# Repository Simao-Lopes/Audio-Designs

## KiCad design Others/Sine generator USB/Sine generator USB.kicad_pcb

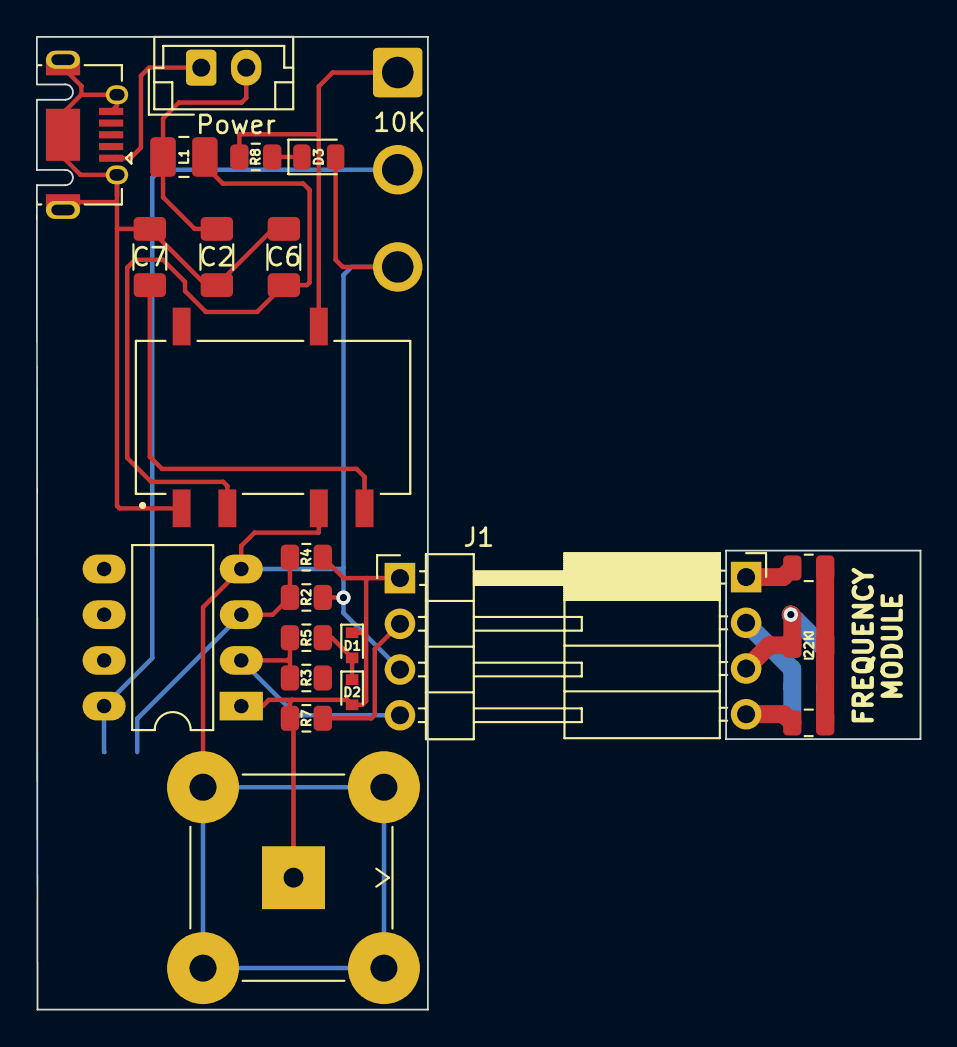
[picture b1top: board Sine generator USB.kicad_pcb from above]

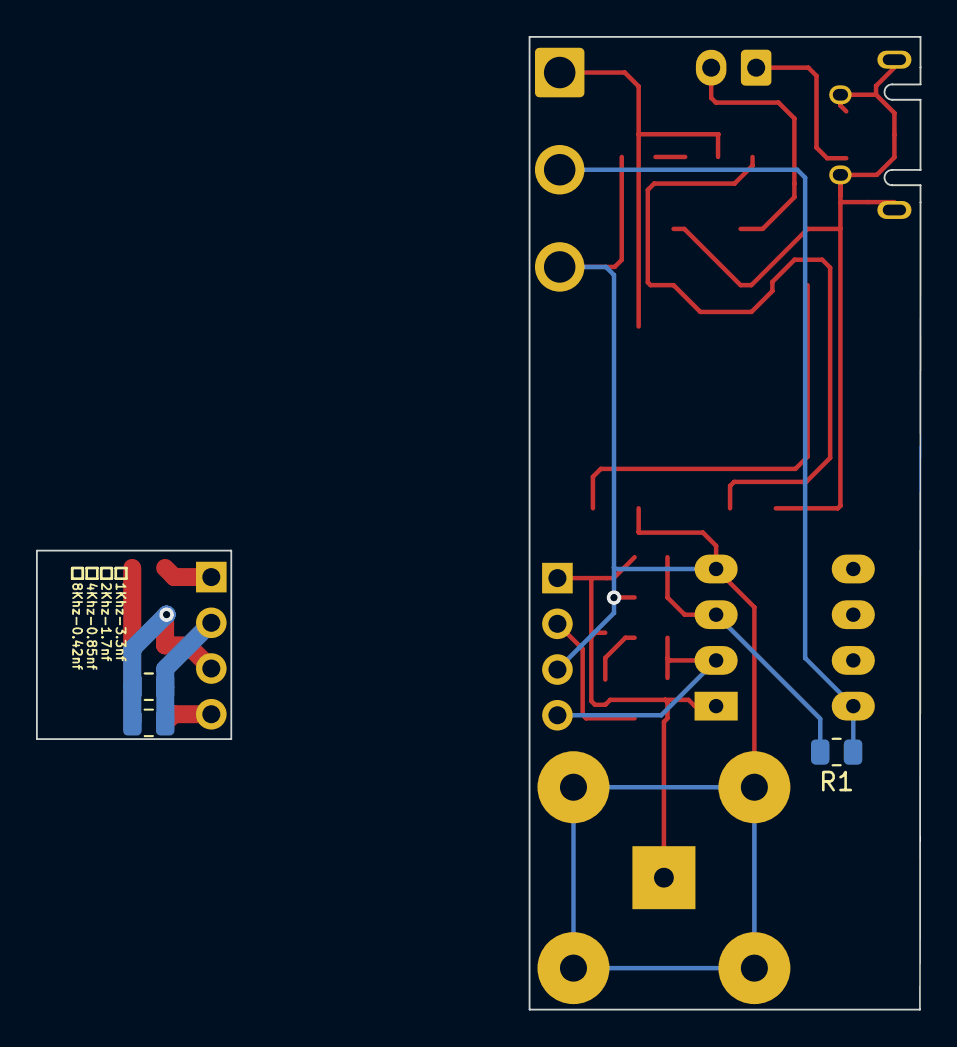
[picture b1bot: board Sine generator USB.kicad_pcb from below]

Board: 2 copper layers, 49.1 x 54.0 mm, 27 parts (3 on the bottom side), 19 nets.

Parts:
10K: 10K; SolderWire-1sqmm_1x03_P5.4mm_D1.4mm_OD2.7mm
22K: 22k; R_0805_2012Metric
C1, C3, C4, C5: 0.01uf; R_0805_2012Metric
C2, C6: 4u7; C_1206_3216Metric_Pad1.33x1.80mm_HandSolder
C7: 1nf/4kv; C_1206_3216Metric_Pad1.33x1.80mm_HandSolder
D1, D2: 1N4148; D_SOD-523
D3: LED; LED_0805_2012Metric
J1: Board In; PinHeader_1x04_P2.54mm_Horizontal
J2: Freq_board; PinSocket_1x04_P2.54mm_Horizontal
J3: Conn_Coaxial; BNC_TEConnectivity_1478035_Horizontal
J4: USB_B_Mini; USB_Micro-AB_Molex_47590-0001
L1: 6.8uh; L_1008_2520Metric_Pad1.43x2.20mm_HandSolder
Power: SW_DIP_x01; JST_EH_B2B-EH-A_1x02_P2.50mm_Vertical
R1, R2, R8: 10K; R_0805_2012Metric
R3: 47K; R_0805_2012Metric
R4: 300K; R_0805_2012Metric
R5: 470K; R_0805_2012Metric
R7: 47k; R_0805_2012Metric
U1: LM358; DIP-8_W7.62mm_LongPads
U2: PESE1-S5-D12-M; CONV_PESE1-S5-D12-M

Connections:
/Gnd_board: 22K.2, C1.1, C4.1, J2.3
GND: 10K.3, D3.2 (A), J1.3, J3.2 (Ext), R2.2, U1.4 (V-), U2.4 (0V)
unnamed: C1.2, C4.2, J2.2
unnamed: C2.2, C6.1, C7.1, J4.5 (GND), J4.6 (Shield), U2.1 (VIN-)
unnamed: C3.1, J2.4
unnamed: 22K.1, C3.2, C5.1
unnamed: C5.2, J2.1
unnamed: C6.2, L1.2, U2.2 (VIN+)
unnamed: C7.2, U2.5 (VOUT-)
unnamed: D1.1 (K), D2.2 (A), J1.1, J3.1 (In), R4.2, R7.2, U1.1
unnamed: D1.2 (A), D2.1 (K), R5.2
unnamed: D3.1 (K), R8.1
unnamed: J1.2, R3.2, R7.1
unnamed: J1.4, R3.1, R5.1, U1.2 (-)
unnamed: 10K.2, R1.1, U1.8 (V+)
unnamed: R1.2, R2.1, R4.1, U1.3 (+)
unnamed: 10K.1, R8.2, U2.7 (VOUT+)
unnamed: J4.1 (VBUS), Power.1
unnamed: C2.1, L1.1, Power.2

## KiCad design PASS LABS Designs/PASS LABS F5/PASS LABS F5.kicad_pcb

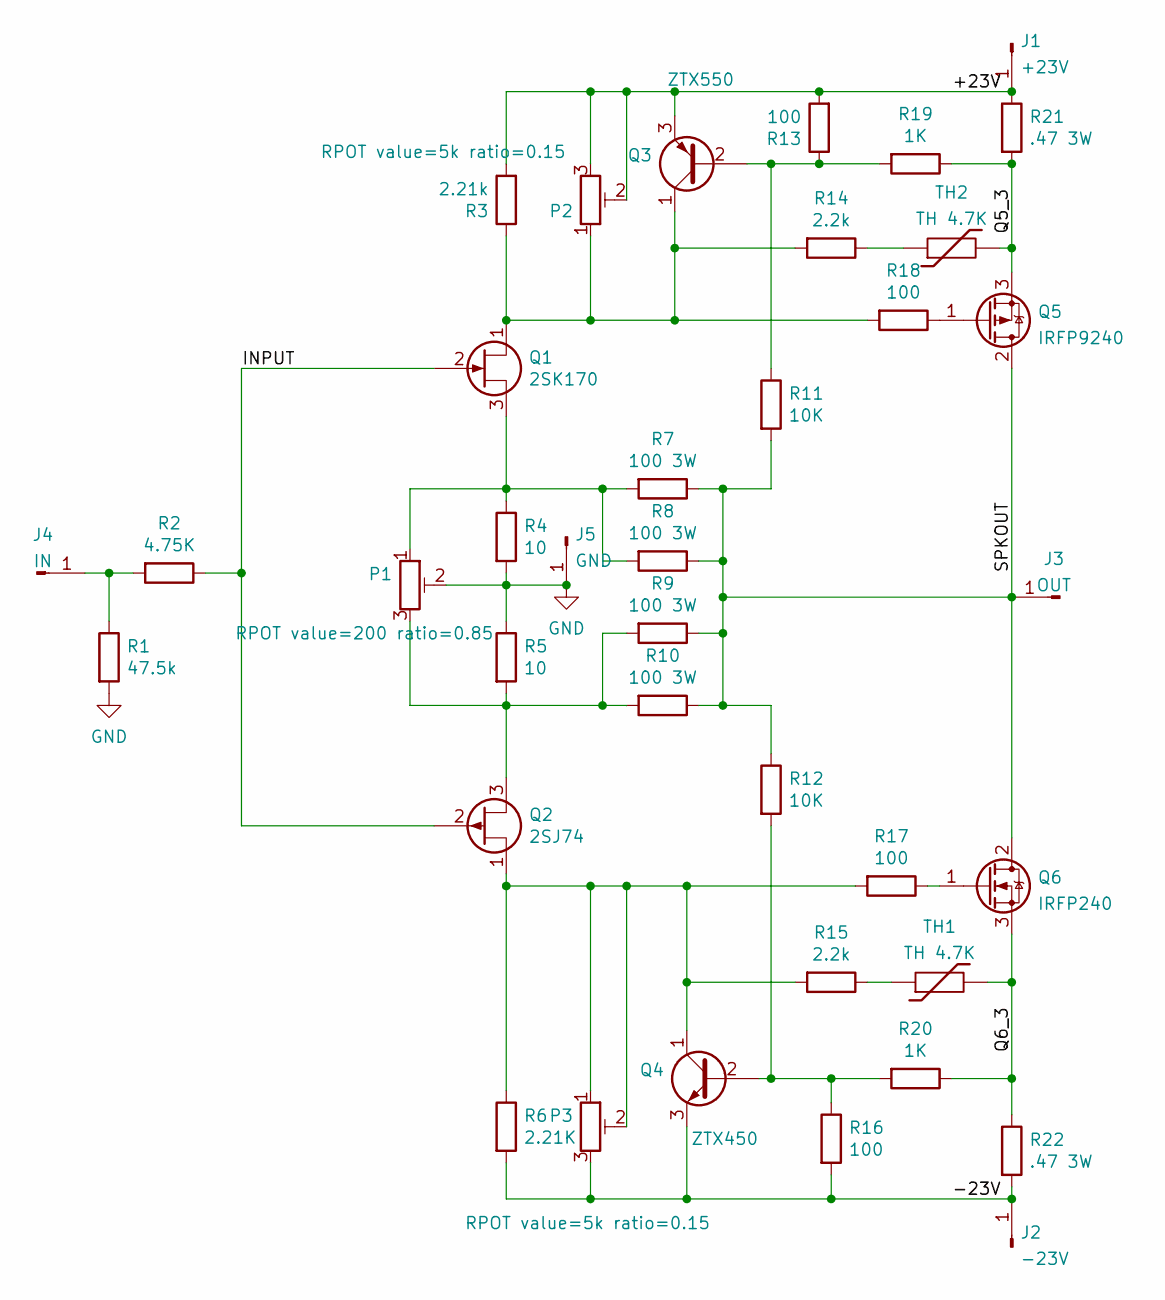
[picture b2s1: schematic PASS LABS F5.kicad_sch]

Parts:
J1: +23V; M4_Screw_Terminal
J2: -23V; M4_Screw_Terminal
J3: OUT; M4_Screw_Terminal
J4: IN; M4_Screw_Terminal
J5: GND; M4_Screw_Terminal
P1: 200; TRIM_3362P-1-103
P2: 5K; TRIM_3362P-1-103
P3: 5k; TRIM_3362P-1-103
Q1: 2SK170; TO-92L_Wide
Q2: 2SJ74; TO-92L_Wide
Q3: ZTX550; TO-92L_Wide
Q4: ZTX450; TO-92L_Wide
Q5: IRFP9240; TO-247-3_Vertical
Q6: IRFP240; TO-247-3_Vertical
R1: 47.5k; R_Axial_DIN0207_L6.3mm_D2.5mm_P10.16mm_Horizontal
R2: 4.75K; R_Axial_DIN0207_L6.3mm_D2.5mm_P10.16mm_Horizontal
R3: 2.21k; R_Axial_DIN0207_L6.3mm_D2.5mm_P10.16mm_Horizontal
R4, R5: 10; R_Axial_DIN0207_L6.3mm_D2.5mm_P10.16mm_Horizontal
R6: 2.21K; R_Axial_DIN0207_L6.3mm_D2.5mm_P10.16mm_Horizontal
R7, R8, R9, R10: 100 3W; R_Axial_DIN0411_L9.9mm_D3.6mm_P15.24mm_Horizontal
R11, R12: 10K; R_Axial_DIN0207_L6.3mm_D2.5mm_P10.16mm_Horizontal
R13, R16, R17, R18: 100; R_Axial_DIN0207_L6.3mm_D2.5mm_P10.16mm_Horizontal
R14, R15: 2.2k; R_Axial_DIN0207_L6.3mm_D2.5mm_P10.16mm_Horizontal
R19, R20: 1K; R_Axial_DIN0207_L6.3mm_D2.5mm_P10.16mm_Horizontal
R21, R22: .47 3W; R_Axial_DIN0411_L9.9mm_D3.6mm_P15.24mm_Horizontal
TH1, TH2: TH 4.7K; C_Disc_D3.0mm_W2.0mm_P2.50mm

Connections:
/+23V: J1.1, P2.2, P2.3, Q3.3 (E), R3.2, R13.2, R21.1
/-23V: J2.1, P3.3, Q4.3 (E), R6.2, R16.2, R22.2
/INPUT: Q1.2 (G), Q2.2 (G), R2.1
/Q5_3: Q5.3 (S), R19.1, R21.2, TH2.2
/Q6_3: Q6.3 (S), R20.1, R22.1, TH1.2
/SPKOUT: J3.1, Q5.2 (D), Q6.2 (D), R7.1, R8.1, R9.1, R10.1, R11.2, R12.1
GND: J5.1, P1.2, R1.2, R4.2, R5.1; also elsewhere on the board
unnamed 7: J4.1, R1.1, R2.2; also elsewhere on the board
unnamed: P1.1, Q1.3 (S), R4.1, R7.2, R8.2
unnamed: P1.3, Q2.3 (D), R5.2, R9.2, R10.2
unnamed: P2.1, Q1.1 (D), Q3.1 (C), R3.1, R14.2, R18.2
unnamed: P3.1, P3.2, Q2.1 (S), Q4.1 (C), R6.1, R15.2, R17.2
unnamed: Q3.2 (B), R11.1, R13.1, R19.2
unnamed: Q4.2 (B), R12.2, R16.1, R20.2
unnamed: Q5.1 (G), R18.1
unnamed: Q6.1 (G), R17.1
unnamed: R14.1, TH2.1
unnamed: R15.1, TH1.1

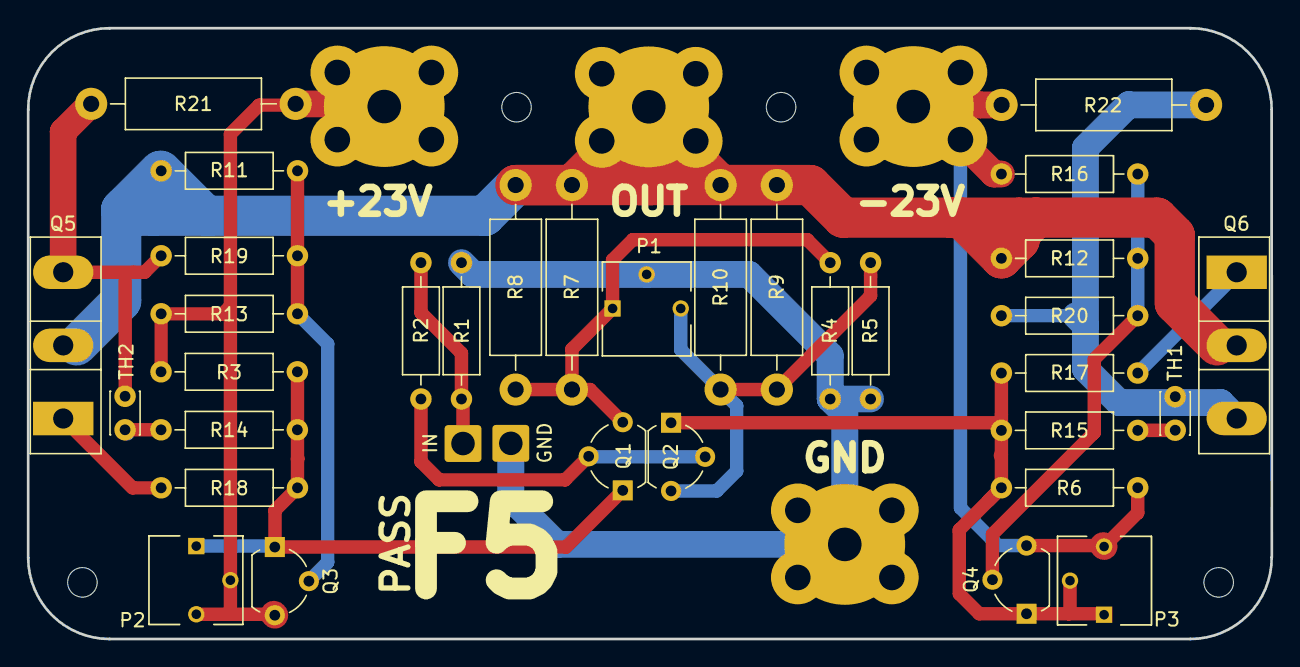
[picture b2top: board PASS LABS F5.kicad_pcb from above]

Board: 2 copper layers, 92.7 x 45.5 mm, 39 parts (0 on the bottom side), 18 nets.

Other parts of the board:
GND: IN; SolderWire-1sqmm_1x01_D1.4mm_OD2.7mm
IN: IN; SolderWire-1sqmm_1x01_D1.4mm_OD2.7mm

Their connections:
GND: GND.1; also elsewhere on the board
unnamed 7: IN.1; also elsewhere on the board

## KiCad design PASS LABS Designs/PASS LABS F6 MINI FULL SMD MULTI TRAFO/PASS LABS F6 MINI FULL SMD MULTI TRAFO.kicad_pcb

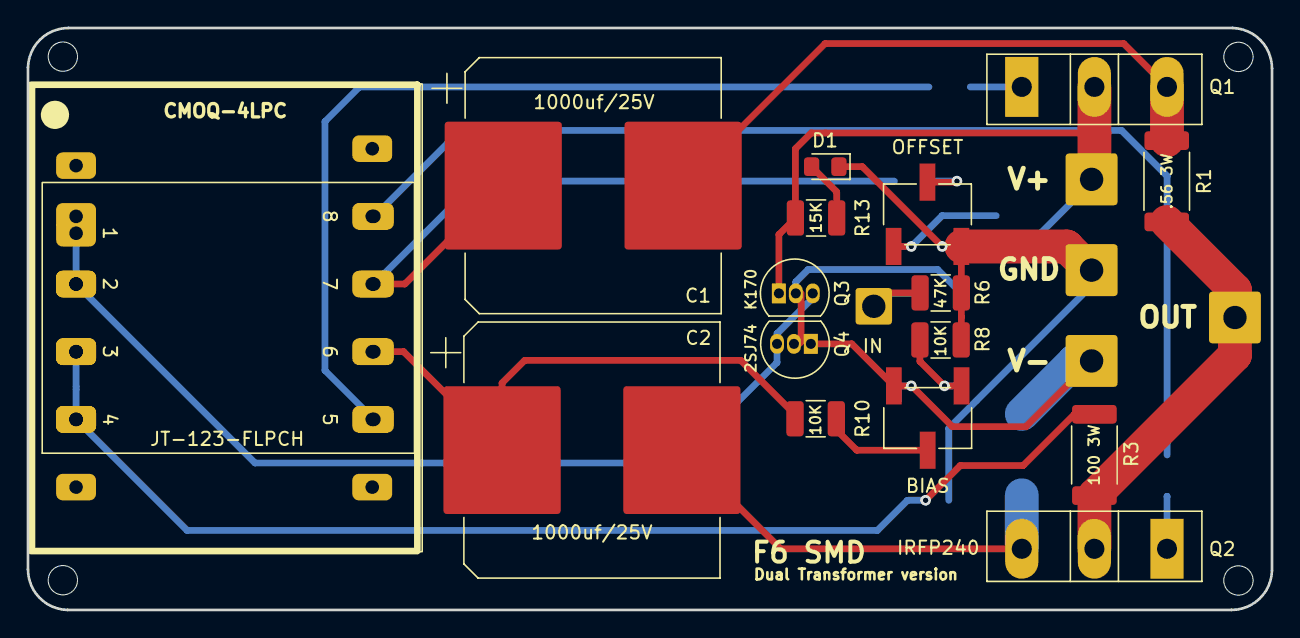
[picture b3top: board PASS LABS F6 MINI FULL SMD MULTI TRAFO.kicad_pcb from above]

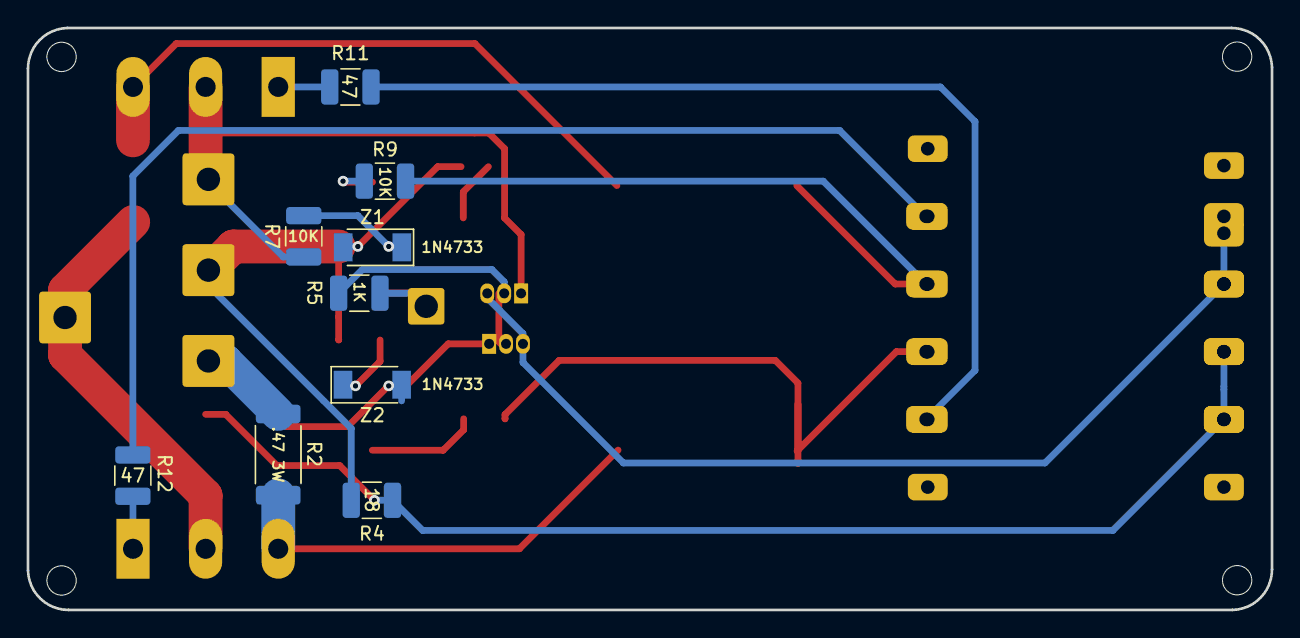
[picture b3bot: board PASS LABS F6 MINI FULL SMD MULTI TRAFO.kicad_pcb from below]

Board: 2 copper layers, 93.4 x 43.7 mm, 30 parts (9 on the bottom side), 21 nets.

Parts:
BIAS: R_Potentiometer_US; Potentiometer_Bourns_3269W_Vertical
C1, C2: 1000uf/25V; CP_Elec_18x17.5
D1: LED; LED_0805_2012Metric_Pad1.15x1.40mm_HandSolder
GND: GND; SolderWire-1sqmm_1x01_D1.4mm_OD3.9mm
IN: SG IN; SolderWire-1sqmm_1x01_D1.4mm_OD2.7mm
OFFSET: R_Potentiometer_US; Potentiometer_Bourns_3269W_Vertical
OUT: OUT; SolderWire-1sqmm_1x01_D1.4mm_OD3.9mm
Q1, Q2: IRFP240; TO-247-3_Vertical
Q3: K170; TO-92L_Inline
Q4: 2SJ74; TO-92L_Inline
R1: .56 3W; R_2512_6332Metric_Pad1.40x3.35mm_HandSolder
R2: .47 3W; R_2512_6332Metric_Pad1.40x3.35mm_HandSolder
R3: 100 3W; R_2512_6332Metric_Pad1.40x3.35mm_HandSolder
R4: 18; R_1210_3225Metric_Pad1.30x2.65mm_HandSolder
R5: 1K; R_1210_3225Metric_Pad1.30x2.65mm_HandSolder
R6: 47K; R_1210_3225Metric_Pad1.30x2.65mm_HandSolder
R7, R8, R9, R10: 10K; R_1210_3225Metric_Pad1.30x2.65mm_HandSolder
R11, R12: 47; R_1210_3225Metric_Pad1.30x2.65mm_HandSolder
R13: 15K; R_1210_3225Metric_Pad1.30x2.65mm_HandSolder
T1: JT-123-FLPCH
V+: +23V; SolderWire-1sqmm_1x01_D1.4mm_OD3.9mm
V-: -23V; SolderWire-1sqmm_1x01_D1.4mm_OD3.9mm
Z1, Z2: 1N4733; D_SOD-128

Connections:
5: R11.1, T1.5
6: C2.1, R10.1, T1.6
7: C1.1, R9.2, T1.7
8: R12.2, T1.8
/1: Q3.3 (S), Q4.3 (D), T1.1, T1.2
GND: D1.1 (K), GND.1, OFFSET.3, R4.1, R6.1, R8.2, Z1.2 (A)
unnamed: Q1.2 (D), Q3.1 (D), R7.1, R13.1, V+.1
unnamed: BIAS.3, Q4.1 (S), R2.1, V-.1, Z2.2 (A)
unnamed: C1.2, Q1.3 (S), R1.2
unnamed: C2.2, Q2.3 (S), R2.2
unnamed: D1.2 (A), R13.2
unnamed: OUT.1, Q2.2 (D), R1.1, R3.2
unnamed: OFFSET.1, R7.2, Z1.1 (K)
unnamed: OFFSET.2, R9.1
unnamed: BIAS.1, R8.1, Z2.1 (K)
unnamed: BIAS.2, R10.2
unnamed: Q1.1 (G), R11.2
unnamed: Q2.1 (G), R12.1
unnamed: Q3.2 (G), Q4.2 (G), R5.2
unnamed: R3.1, R4.2, T1.3, T1.4
unnamed: IN.1, R5.1, R6.2

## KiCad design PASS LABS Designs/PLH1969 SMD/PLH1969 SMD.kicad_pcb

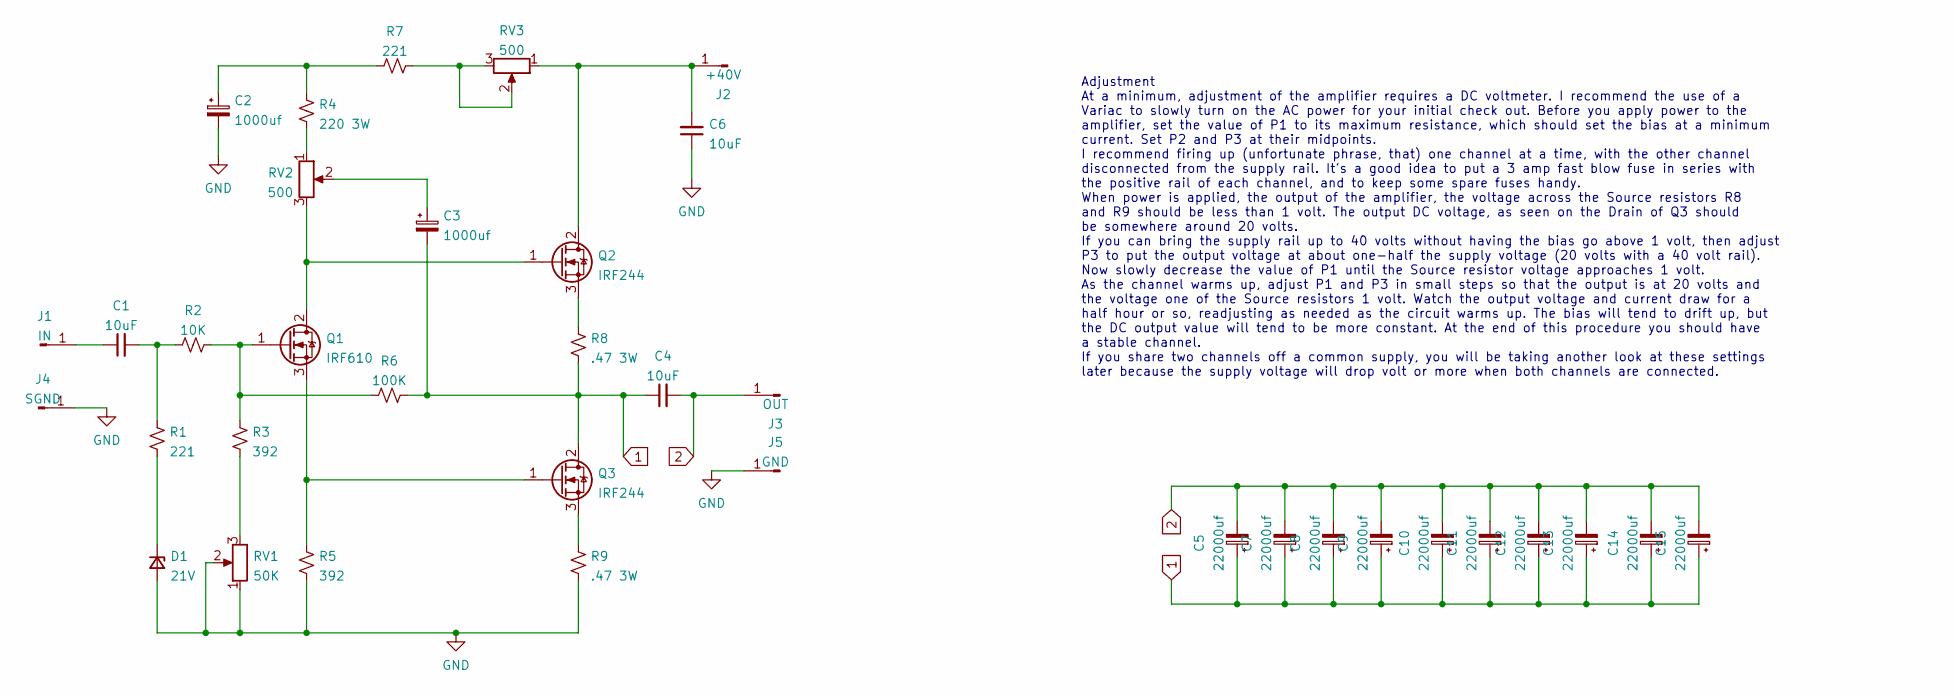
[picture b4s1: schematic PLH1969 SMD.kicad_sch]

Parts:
C1, C4, C6: 10uF; C_Rect_L18.0mm_W9.0mm_P15.00mm_FKS3_FKP3
C2, C3: 1000uf; CP_Elec_18x22
C5, C7, C8, C9, C10, C11, C12, C13, C14, C15: 22000uf; CP_Elec_18x22
D1: 21V; D_1206_3216Metric
J1: IN; Spade Conector 6.3mm TE_1217861
J2: +40V; Spade Conector 6.3mm TE_1217861
J3: OUT; Spade Conector 6.3mm TE_1217861
J4: SGND; Spade Conector 6.3mm TE_1217861
J5: GND; Spade Conector 6.3mm TE_1217861
Q1: IRF610; TO-263-2
Q2, Q3: IRF244; TO-247-3_Vertical
R1, R7: 221; R_1206_3216Metric
R2: 10K; R_1206_3216Metric
R3, R5: 392; R_1206_3216Metric
R4: 220 3W; R_2512_6332Metric
R6: 100K; R_1206_3216Metric
R8, R9: .47 3W; R_2512_6332Metric
RV1: 50K; Potentiometer_Bourns_3296W_Vertical
RV2, RV3: 500; Potentiometer_Bourns_3296W_Vertical

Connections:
1: C3.2, C4.1, C5.1, C7.1, C8.1, C9.1, C10.1, C11.1, C12.1, C13.1, C14.1, C15.1, Q3.2 (D), R6.2, R8.2
2: C4.2, C5.2, C7.2, C8.2, C9.2, C10.2, C11.2, C12.2, C13.2, C14.2, C15.2, J3.1
GND: C2.2, C6.1, D1.2 (A), J4.1, J5.1, R5.2, R9.2, RV1.1, RV1.2; also elsewhere on the board
unnamed: C1.1, J1.1
unnamed: C1.2, R1.1, R2.1
unnamed: C2.1, R4.1, R7.1
unnamed: C3.1, RV2.2
unnamed: C6.2, J2.1, Q2.2 (D), RV3.1
unnamed: D1.1 (K), R1.2
unnamed: Q1.1 (G), R2.2, R3.1, R6.1
unnamed: Q1.2 (D), Q2.1 (G), RV2.3
unnamed: Q1.3 (S), Q3.1 (G), R5.1
unnamed: Q2.3 (S), R8.1
unnamed: Q3.3 (S), R9.1
unnamed: R3.2, RV1.3
unnamed: R4.2, RV2.1
unnamed: R7.2, RV3.2, RV3.3

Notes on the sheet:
Adjustment At a minimum, adjustment of the amplifier requires a DC voltmeter. I recommend the use of a Variac to slowly turn on the AC power for your initial check out. Before you apply power to the amplifier, set the value of P1 to its maximum resistance, which should set the bias at a minimum cur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

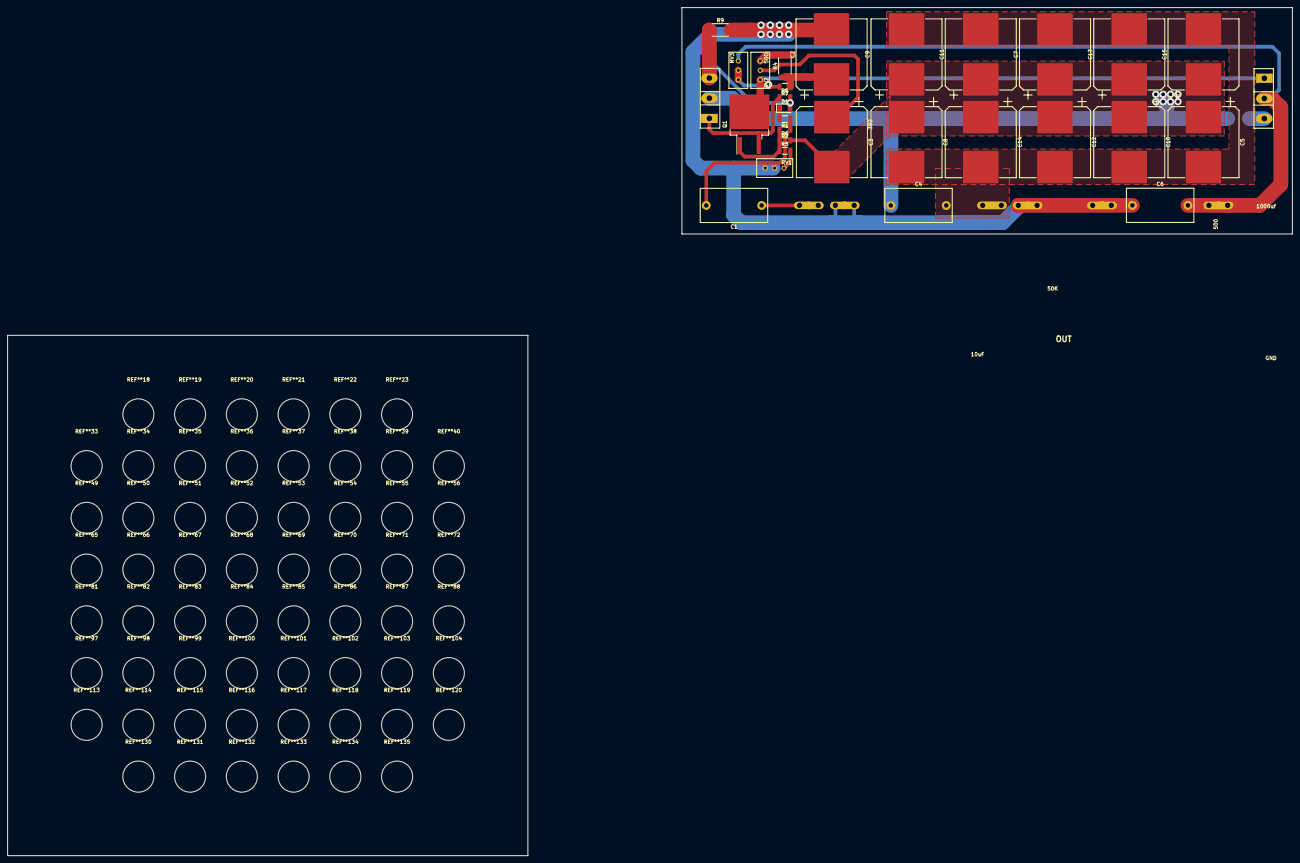
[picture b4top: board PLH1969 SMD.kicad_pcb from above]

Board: 2 copper layers, 165.2 x 61.2 mm, 37 parts (1 on the bottom side), 17 nets.

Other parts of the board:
J5#2: GND; Spade Conector 6.3mm TE_1217861

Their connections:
GND: J5#2.1; also elsewhere on the board

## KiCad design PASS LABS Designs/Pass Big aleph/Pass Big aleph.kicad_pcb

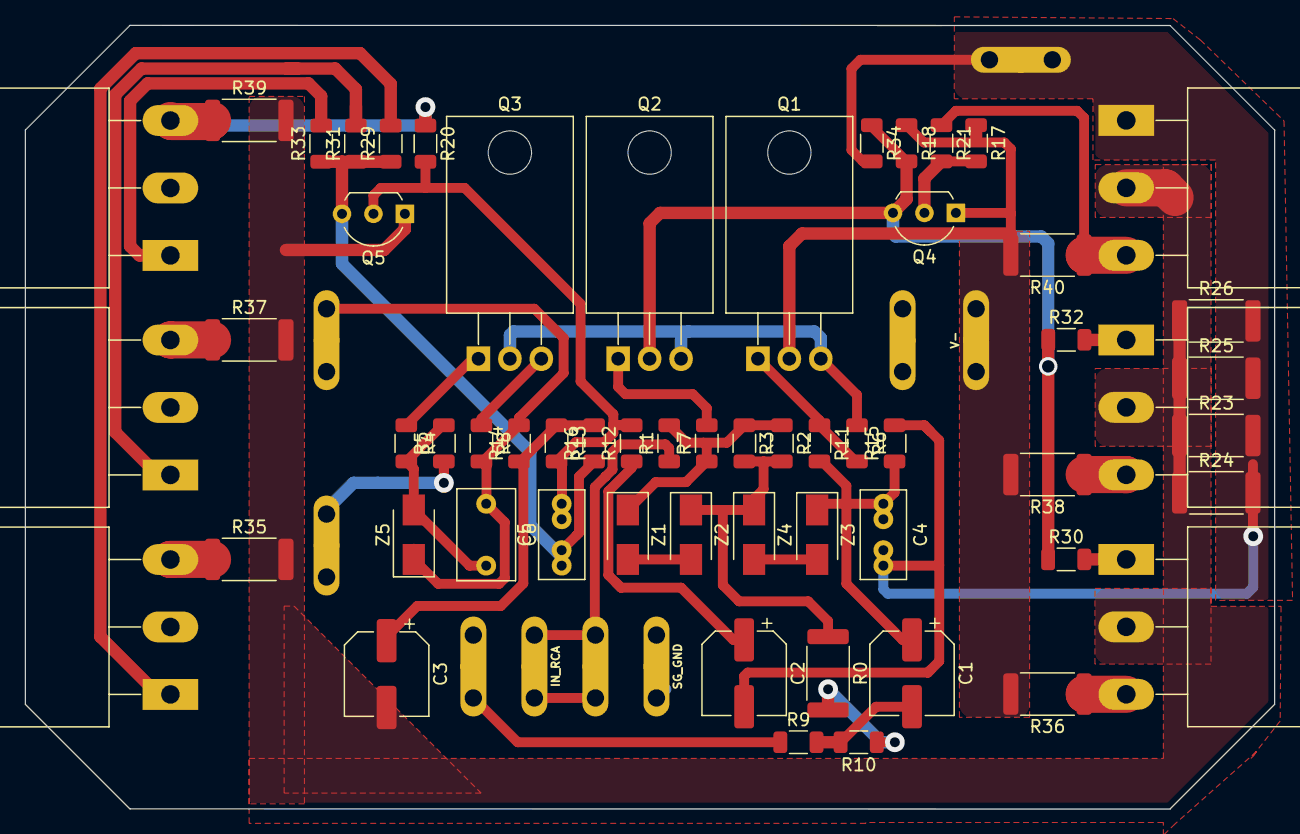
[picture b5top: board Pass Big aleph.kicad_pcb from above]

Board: 2 copper layers, 100.9 x 63.3 mm, 68 parts (0 on the bottom side), 36 nets.

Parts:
C1, C2, C3: 220uf; CP_Elec_6.3x5.4_Nichicon
C4: 10PF; C_Rect_L7.0mm_W3.5mm_P2.50mm_P5.00mm
C5: 1NF; C_Rect_L7.0mm_W3.5mm_P2.50mm_P5.00mm
C6: 47NF; C_Rect_L7.2mm_W4.5mm_P5.00mm_FKS2_FKP2_MKS2_MKP2
GND: Conn_01x01_Male; Spade Conector 6.3mm TE_1217861
IN+: Conn_01x01_Male; Spade Conector 6.3mm TE_1217861
IN-: Conn_01x01_Male; Spade Conector 6.3mm TE_1217861
IN_RCA: Conn_01x01_Male; Spade Conector 6.3mm TE_1217861
OUT: Conn_01x01_Male; Spade Conector 6.3mm TE_1217861
OUT_GND: Conn_01x01_Male; Spade Conector 6.3mm TE_1217861
Q1, Q2, Q3: IRFP9610; TO-220-3_Horizontal_TabDown
Q4, Q5: ZTX450; TO-92L_Inline_Wide
Q8, Q9, Q10, Q11, Q12, Q13: IRFP240; TO-247-3_Horizontal_TabDown
R0: 3/3W; R_2512_6332Metric
R1: 10K; R_1206_3216Metric
R2, R15: 100K; R_1206_3216Metric
R3: 68.1K; R_1206_3216Metric
R4, R7, R8, R11, R21, R29, R30, R31, R32, R33, R34: 221; R_1206_3216Metric
R5: 4.75K; R_1206_3216Metric
R6: Adjust; R_1206_3216Metric
R9: 10k; R_1206_3216Metric
R10: 68.1k; R_1206_3216Metric
R12: 825; R_1206_3216Metric
R13: 47.5K; R_1206_3216Metric
R14, R16: 1.5K; R_1206_3216Metric
R17, R18: 392; R_1206_3216Metric
R20: 1K; R_1206_3216Metric
R23, R24, R25, R26: 0.47/3W; R_2512_6332Metric
R35, R36, R37, R38, R39, R40: .47/3W; R_2512_6332Metric
SG_GND: Conn_01x01_Male; Spade Conector 6.3mm TE_1217861
V+: Conn_01x01_Male; Spade Conector 6.3mm TE_1217861
V-: Conn_01x01_Male; Spade Conector 6.3mm TE_1217861
Z1, Z2, Z3, Z4, Z5: 9.1V; D_SMA

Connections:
/+Gate: C5.1, Q5.3 (C), R16.1, R29.1, R31.1, R33.1
/+Sense: Q13.3 (S), R20.1, R39.1
/-Gate: Q2.2 (D), Q4.3 (C), R18.2, R30.1, R32.1, R34.1
/-Sense: Q12.3 (S), R21.1, R40.1
/Common: C3.2, Q5.1 (E), Q8.2 (D), Q10.2 (D), Q12.2 (D), R23.1, R24.1, R25.1, R26.1, R35.2, R37.2, R39.2
GND: GND.1, OUT_GND.1, R0.2, R5.1, R10.1, SG_GND.1
unnamed: C1.1, C4.1, R11.2, R15.1, Z3.1 (K)
unnamed: C1.2, R9.2, R10.2
unnamed: C2.1, R12.1
unnamed: C2.2, C4.2, OUT.1, Q12.1 (G), R15.2, R23.2, R24.2, R25.2, R26.2, R34.2
unnamed: C3.1, R13.1, R14.1, R16.2
unnamed: C5.2, Q5.2 (B), R12.2, R13.2, R20.2
unnamed: C6.1, Q9.2 (D), Q11.2 (D), Q13.2 (D), R8.2, R14.2, V+.1, Z5.1 (K)
unnamed: C6.2, R4.2, R5.2, Z5.2 (A)
unnamed: IN+.1, IN_RCA.1, R1.1
unnamed: IN-.1, R9.1
unnamed: Q1.1 (G), R6.2, R11.1
unnamed: Q1.2 (D), Q4.1 (E), R17.1, R18.1, R36.2, R38.2, R40.2, V-.1
unnamed: Q1.3 (S), Q2.3 (S), Q3.2 (D), R6.1
unnamed: Q2.1 (G), R7.2
unnamed: Q3.1 (G), R4.1
unnamed: Q3.3 (S), R8.1
unnamed: Q4.2 (B), R17.2, R21.2
unnamed: Q8.1 (G), R30.2
unnamed: Q8.3 (S), R36.1
unnamed: Q9.1 (G), R29.2
unnamed: Q9.3 (S), R35.1
unnamed: Q10.1 (G), R32.2
unnamed: Q10.3 (S), R38.1
unnamed: Q11.1 (G), R31.2
unnamed: Q11.3 (S), R37.1
unnamed: Q13.1 (G), R33.2
unnamed: R0.1, R2.2, R3.2, Z2.1 (K), Z4.1 (K)
unnamed: R1.2, R2.1, R3.1, R7.1, Z1.1 (K)
unnamed: Z1.2 (A), Z2.2 (A)
unnamed: Z3.2 (A), Z4.2 (A)

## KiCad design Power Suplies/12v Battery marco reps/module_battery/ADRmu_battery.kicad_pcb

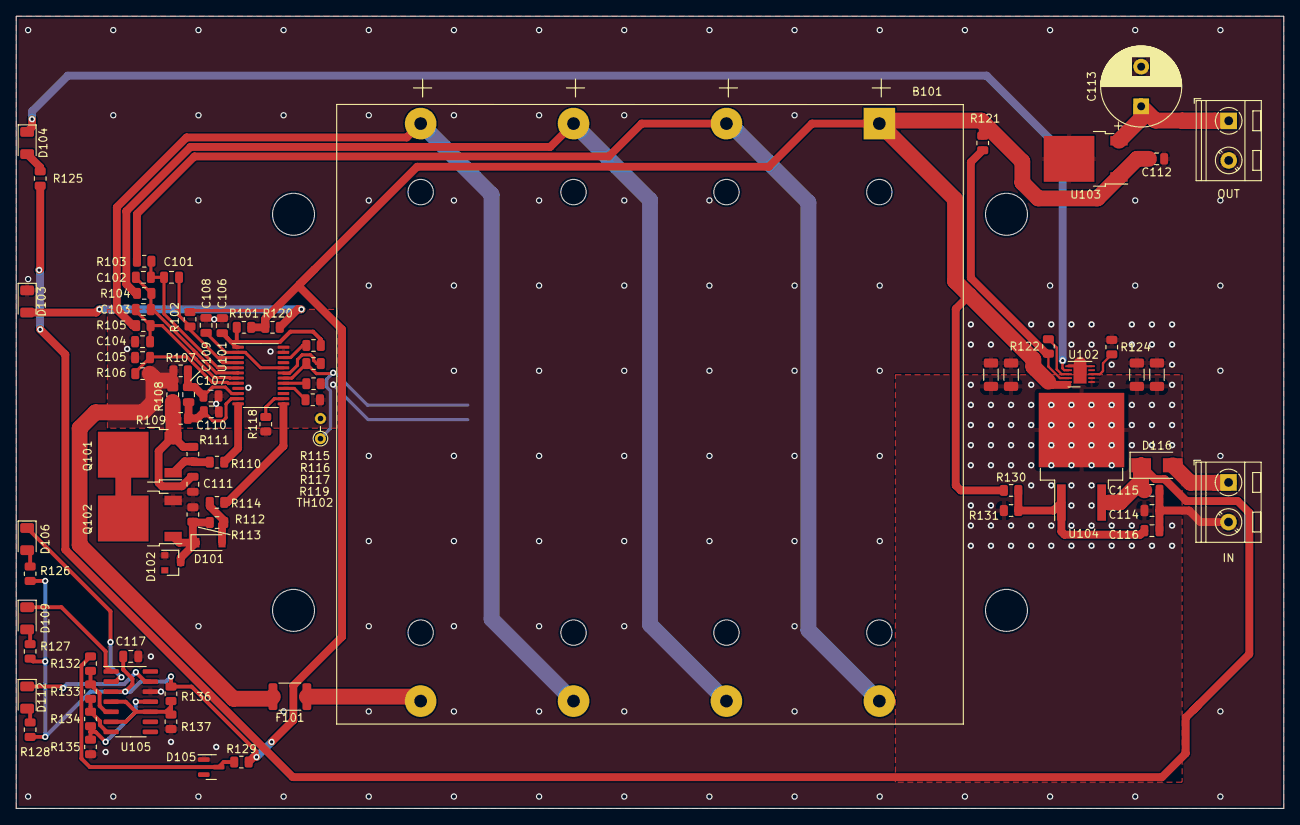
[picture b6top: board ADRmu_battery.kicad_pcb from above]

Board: 2 copper layers, 160.0 x 100.0 mm, 83 parts (1 on the bottom side), 51 nets.

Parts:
B101: BK-18650-PC8
C101, C102, C103, C104, C105, C106, C108, C114, C115, C116: 1u 50V; C_0805_2012Metric
C107, C109, C110, C111, C112, C117: 100n 50V; C_0805_2012Metric
C113: 220u 16V; CP_Radial_D10.0mm_P5.00mm
D101: 1N4148; D_SOD-123
D102: 16V; D_SOT-23_ANK
D103, D104, D106, D109, D112: LT Y8SG-V2AB-36; LED_1206_3216Metric
D105: BZX84C10; SOT-23
D116: RS1D-13-F; D_SMA
F101: 2A; Fuse_1812_4532Metric
H101, H102, H103, H104: MountingHole; MountingHole_5.3mm_M5
HS101, HS102, HS103, HS104: THJP1206AST1; C_1206_3216Metric
IN: TerminalBlock_RND_205-00045_1x02_P5.00mm_Horizont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; TerminalBlock_RND_205-00045_1x02_P5.00mm_Horizontal
OUT: TerminalBlock_RND_205-00045_1x02_P5.00mm_Horizont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; TerminalBlock_RND_205-00045_1x02_P5.00mm_Horizontal
Q101, Q102: Q_NMOS_GDS; TO-252-2
R101: 1k; R_0805_2012Metric
R102, R103, R104, R105, R106: 33; R_0805_2012Metric
R107, R109: 100; R_0805_2012Metric
R108: 60mR; R_0805_2012Metric
R110, R114, R130: 5k1; R_0805_2012Metric
R111: 10M; R_0805_2012Metric
R112: 1M; R_0805_2012Metric
R113: 3M; R_0805_2012Metric
R115, R116, R119, R129, R131, R136, R137: 10k; R_0805_2012Metric
R117: 200k; R_0805_2012Metric
R118: 470k; R_0805_2012Metric
R120, R125, R126, R127, R128: 49k9; R_0805_2012Metric
R121: 9.1M; R_0805_2012Metric
R122: 680k; R_0805_2012Metric
R124: 1k2; R_0805_2012Metric
R132: 22k; R_0805_2012Metric
R133, R134: 6k8; R_0805_2012Metric
R135: 82k; R_0805_2012Metric
TH101: CMFB3435103FNT; R_0805_2012Metric
TH102: Alternative 10k NTC; R_Axial_DIN0204_L3.6mm_D1.6mm_P2.54mm_Vertical
U101: BQ7791500; TSSOP-24_4.4x7.8mm_P0.65mm
U102: LTC4079; DFN-10-1EP_3x3mm_P0.5mm_EP1.65x2.38mm
U103: L7812; TO-252-2
U104: LM317_TO-263; TO-263-2
U105: LM339; SOIC-14_3.9x8.7mm_P1.27mm

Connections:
+BATT: B101.1 (+), C112.2, C117.2, R101.1, R102.1, R120.1, R121.2, R126.2, R127.2, R128.2, R129.2, R130.2, R136.2, U102.10 (BAT), U103.1 (IN), U105.3 (V+)
-BATT: B101.8 (-), F101.1
/-i/o: C111.2, C112.1, C113.2, C114.2, C115.2, C116.2, C117.1, D102.2 (A), D103.1 (K), D105.1 (A), HS101.2, HS102.2, HS103.2, HS104.2, IN.2, OUT.2, Q102.3 (S), R113.1, R118.1, R124.1, R135.1, R137.1, U102.5 (NTC), U102.6 (TIMER), U102.11 (GND), U103.2 (GND), U105.12 (V-)
/AVDD: C108.2, U101.2 (AVDD), U101.20 (CCFG)
/dropped_in+: C114.1, HS101.1, HS102.1, HS103.1, HS104.1, R131.1, U102.1 (VDD), U102.2 (EN), U104.2 (VO)
/in+: D116.2 (A), IN.1
GND: C104.2, C105.2, C106.2, C107.1, C108.1, C110.1, F101.2, R106.1, R107.1, R108.1, R117.1, R119.1, TH101.2, TH102.2, U101.9 (VSS), U101.23 (CTRC), U101.24 (CTRD)
unnamed: B101.2 (-), B101.3 (+), R103.1
unnamed: B101.4 (-), B101.5 (+), R104.1
unnamed: B101.6 (-), B101.7 (+), R105.1
unnamed: C101.1, R102.2, U101.3 (VC5), U101.4 (VC4)
unnamed: C101.2, C102.1, R103.2, U101.5 (VC3)
unnamed: C102.2, C103.1, R104.2, U101.6 (VC2)
unnamed: C103.2, C104.1, R105.2, U101.7 (VC1)
unnamed: C105.1, R106.2, U101.8 (VC0)
unnamed: C106.1, R101.2, R115.2, U101.1 (VDD)
unnamed: C107.2, C109.1, R107.2, U101.10 (SRP)
unnamed: C109.2, C110.2, R109.2, U101.11 (SRN)
unnamed: C111.1, Q101.3 (S), R108.2, R109.1, R111.1
unnamed: C113.1, OUT.1, U103.3 (OUT)
unnamed: C115.1, D116.1 (K), R125.1, U104.3 (VI)
unnamed: C116.1, R130.1, R131.2, U104.1 (ADJ)
unnamed: D101.1 (K), D102.1 (K), Q102.1 (G), R112.2, R113.2
unnamed: D101.2 (A), R112.1, R114.2
unnamed: D103.2 (A), R120.2
unnamed: D104.1 (K), U102.7 (~CHRG)
unnamed: D104.2 (A), R125.2
unnamed: D105.3 (K), R129.1, R132.2
unnamed: D106.1 (K), U105.2
unnamed: D106.2 (A), R126.1
unnamed: D109.1 (K), U105.1
unnamed: D109.2 (A), R127.1
unnamed: D112.1 (K), U105.13
unnamed: D112.2 (A), R128.1
unnamed: Q101.1 (G), R110.1, R111.2
unnamed: Q101.2 (D), Q102.2 (D)
unnamed: R110.2, U101.12 (DSG)
unnamed: R114.1, U101.13 (CHG)
unnamed: R115.1, U101.22 (PRES)
unnamed: R116.1, TH101.1, TH102.1, U101.18 (TS)
unnamed: R116.2, U101.19 (VTB)
unnamed: R117.2, U101.17 (OCDP)
unnamed: R118.2, U101.14 (LD)
unnamed: R119.2, U101.16 (CBI)
unnamed: R121.1, R122.2, U102.9 (FB)
unnamed: R122.1, U102.8 (FBG)
unnamed: R124.2, U102.3 (PROG)
unnamed: R132.1, R133.2, U105.5 (+)
unnamed: R133.1, R134.2, U105.7 (+)
unnamed: R134.1, R135.2, U105.11 (+)
unnamed: R136.1, R137.2, U105.4 (-), U105.6 (-), U105.10 (-)

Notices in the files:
parts and their libraries:
Copyright 2016 Accelerated Designs. All rights reserved.
